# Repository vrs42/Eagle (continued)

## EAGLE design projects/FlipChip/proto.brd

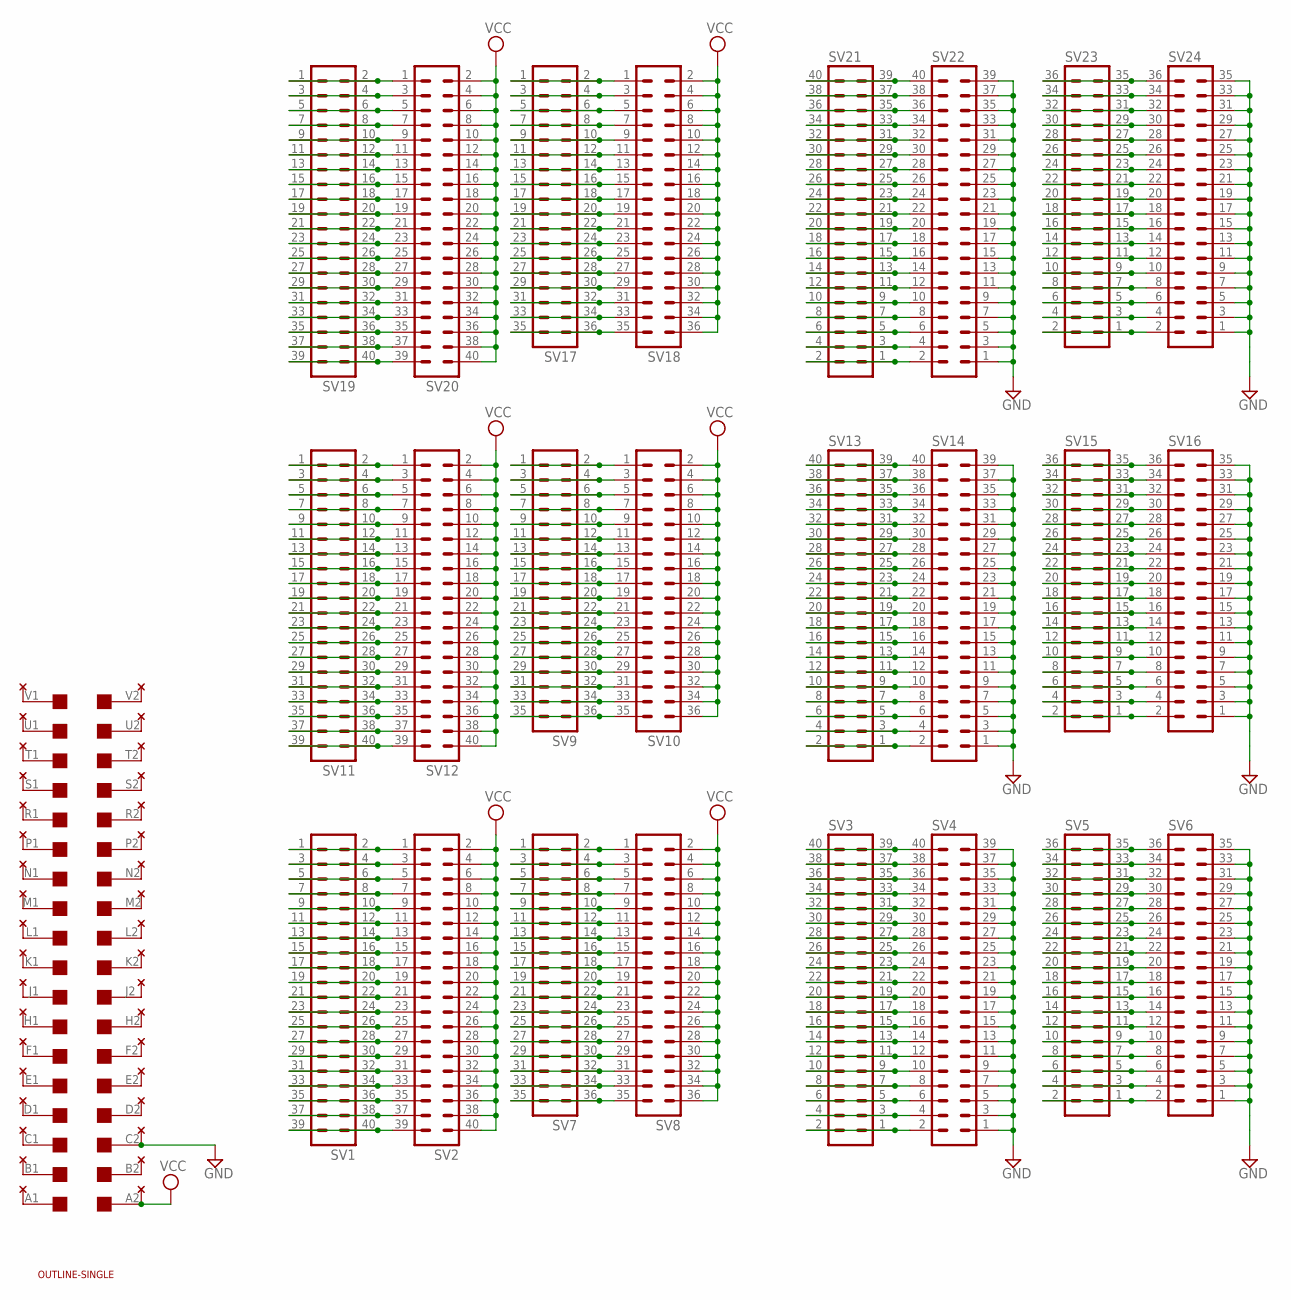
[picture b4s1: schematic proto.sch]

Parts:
SV1, SV2, SV3, SV4, SV11, SV12, SV13, SV14, SV19, SV20, SV21, SV22: MA20-2
SV5, SV6, SV7, SV8, SV9, SV10, SV15, SV16, SV17, SV18, SV23, SV24: MA18-2
U$1: EDGE-2CONNECTOR; EDGE-CON2
U$2: OUTLINE-SINGLE; SINGLE
U$3: THRU-HOLE2A; THRU-HOLEA

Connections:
GND: SV4.1, SV4.3, SV4.5, SV4.7, SV4.9, SV4.11, SV4.13, SV4.15, SV4.17, SV4.19, SV4.21, SV4.23, SV4.25, SV4.27, SV4.29, SV4.31, SV4.33, SV4.35, SV4.37, SV4.39, SV6.1, SV6.3, SV6.5, SV6.7, SV6.9, SV6.11, SV6.13, SV6.15, SV6.17, SV6.19, SV6.21, SV6.23, SV6.25, SV6.27, SV6.29, SV6.31, SV6.33, SV6.35, SV14.1, SV14.3, SV14.5, SV14.7, SV14.9, SV14.11, SV14.13, SV14.15, SV14.17, SV14.19, SV14.21, SV14.23, SV14.25, SV14.27, SV14.29, SV14.31, SV14.33, SV14.35, SV14.37, SV14.39, SV16.1, SV16.3, SV16.5, SV16.7, SV16.9, SV16.11, SV16.13, SV16.15, SV16.17, SV16.19, SV16.21, SV16.23, SV16.25, SV16.27, SV16.29, SV16.31, SV16.33, SV16.35, SV22.1, SV22.3, SV22.5, SV22.7, SV22.9, SV22.11, SV22.13, SV22.15, SV22.17, SV22.19, SV22.21, SV22.23, SV22.25, SV22.27, SV22.29, SV22.31, SV22.33, SV22.35, SV22.37, SV22.39, SV24.1, SV24.3, SV24.5, SV24.7, SV24.9, SV24.11, SV24.13, SV24.15, SV24.17, SV24.19, SV24.21, SV24.23, SV24.25, SV24.27, SV24.29, SV24.31, SV24.33, SV24.35, U$1.C2, U$3.C2
unnamed: U$1.K2, U$3.K2
unnamed: U$1.J2, U$3.J2
unnamed: U$1.H2, U$3.H2
unnamed: U$1.L2, U$3.L2
unnamed: U$1.M2, U$3.M2
unnamed: U$1.N2, U$3.N2
unnamed: U$1.P2, U$3.P2
unnamed: U$1.F2, U$3.F2
unnamed: U$1.E2, U$3.E2
unnamed: U$1.D2, U$3.D2
unnamed: SV1.1, SV1.2, SV2.1
unnamed: U$1.R2, U$3.R2
unnamed: U$1.S2, U$3.S2
unnamed: U$1.B2, U$3.B2
unnamed: SV1.3, SV1.4, SV2.3
unnamed: U$1.T2, U$3.T2
unnamed: U$1.U2, U$3.U2
unnamed: U$1.V2, U$3.V2
unnamed: U$1.A1, U$3.A1
unnamed: U$1.V1, U$3.V1
unnamed: U$1.U1, U$3.U1
unnamed: U$1.T1, U$3.T1
unnamed: U$1.S1, U$3.S1
unnamed: U$1.R1, U$3.R1
unnamed: U$1.P1, U$3.P1
unnamed: U$1.N1, U$3.N1
unnamed: U$1.M1, U$3.M1
unnamed: U$1.L1, U$3.L1
unnamed: U$1.K1, U$3.K1
unnamed: U$1.J1, U$3.J1
unnamed: U$1.H1, U$3.H1
unnamed: U$1.F1, U$3.F1
unnamed: U$1.E1, U$3.E1
unnamed: U$1.D1, U$3.D1
unnamed: U$1.C1, U$3.C1
unnamed: U$1.B1, U$3.B1
unnamed: SV1.5, SV1.6, SV2.5
unnamed: SV7.1, SV7.2, SV8.1
unnamed: SV7.3, SV7.4, SV8.3
unnamed: SV7.5, SV7.6, SV8.5
unnamed: SV7.7, SV7.8, SV8.7
unnamed: SV7.9, SV7.10, SV8.9
unnamed: SV7.11, SV7.12, SV8.11
unnamed: SV7.13, SV7.14, SV8.13
unnamed: SV1.7, SV1.8, SV2.7
unnamed: SV1.9, SV1.10, SV2.9
unnamed: SV1.11, SV1.12, SV2.11
unnamed: SV1.13, SV1.14, SV2.13
unnamed: SV1.15, SV1.16, SV2.15
unnamed: SV1.17, SV1.18, SV2.17
unnamed: SV1.19, SV1.20, SV2.19
unnamed: SV1.21, SV1.22, SV2.21
unnamed: SV1.23, SV1.24, SV2.23
unnamed: SV1.25, SV1.26, SV2.25
unnamed: SV1.27, SV1.28, SV2.27
unnamed: SV1.29, SV1.30, SV2.29
unnamed: SV1.31, SV1.32, SV2.31
unnamed: SV1.33, SV1.34, SV2.33
unnamed: SV1.35, SV1.36, SV2.35
unnamed: SV1.37, SV1.38, SV2.37
unnamed: SV1.39, SV1.40, SV2.39
unnamed: SV7.15, SV7.16, SV8.15
unnamed: SV7.17, SV7.18, SV8.17
unnamed: SV7.19, SV7.20, SV8.19
unnamed: SV7.21, SV7.22, SV8.21
unnamed: SV7.23, SV7.24, SV8.23
unnamed: SV7.25, SV7.26, SV8.25
unnamed: SV7.27, SV7.28, SV8.27
unnamed: SV7.29, SV7.30, SV8.29
unnamed: SV7.31, SV7.32, SV8.31
unnamed: SV7.33, SV7.34, SV8.33
unnamed: SV7.35, SV7.36, SV8.35
unnamed: SV3.39, SV3.40, SV4.40
unnamed: SV3.37, SV3.38, SV4.38
unnamed: SV3.35, SV3.36, SV4.36
unnamed: SV3.33, SV3.34, SV4.34
unnamed: SV3.31, SV3.32, SV4.32
unnamed: SV3.29, SV3.30, SV4.30
unnamed: SV3.27, SV3.28, SV4.28
unnamed: SV3.25, SV3.26, SV4.26
unnamed: SV3.23, SV3.24, SV4.24
unnamed: SV3.21, SV3.22, SV4.22
unnamed: SV3.19, SV3.20, SV4.20
unnamed: SV3.17, SV3.18, SV4.18
unnamed: SV3.15, SV3.16, SV4.16
unnamed: SV3.13, SV3.14, SV4.14
unnamed: SV3.11, SV3.12, SV4.12
unnamed: SV3.9, SV3.10, SV4.10
unnamed: SV3.7, SV3.8, SV4.8
unnamed: SV3.5, SV3.6, SV4.6
unnamed: SV3.3, SV3.4, SV4.4
unnamed: SV3.1, SV3.2, SV4.2
unnamed: SV11.1, SV11.2, SV12.1
unnamed: SV5.35, SV5.36, SV6.36
unnamed: SV5.33, SV5.34, SV6.34
unnamed: SV5.31, SV5.32, SV6.32
unnamed: SV5.29, SV5.30, SV6.30
unnamed: SV5.27, SV5.28, SV6.28
unnamed: SV5.25, SV5.26, SV6.26
unnamed: SV5.23, SV5.24, SV6.24
unnamed: SV5.21, SV5.22, SV6.22
unnamed: SV5.19, SV5.20, SV6.20
unnamed: SV5.17, SV5.18, SV6.18
unnamed: SV5.15, SV5.16, SV6.16
unnamed: SV5.13, SV5.14, SV6.14
unnamed: SV5.11, SV5.12, SV6.12
unnamed: SV5.9, SV5.10, SV6.10
unnamed: SV5.7, SV5.8, SV6.8
unnamed: SV5.5, SV5.6, SV6.6
unnamed: SV5.3, SV5.4, SV6.4
unnamed: SV5.1, SV5.2, SV6.2
unnamed: SV11.3, SV11.4, SV12.3
unnamed: SV11.5, SV11.6, SV12.5
unnamed: SV11.7, SV11.8, SV12.7
unnamed: SV11.9, SV11.10, SV12.9
unnamed: SV11.11, SV11.12, SV12.11
unnamed: SV11.13, SV11.14, SV12.13
unnamed: SV11.15, SV11.16, SV12.15
unnamed: SV11.17, SV11.18, SV12.17
unnamed: SV11.19, SV11.20, SV12.19
unnamed: SV11.21, SV11.22, SV12.21
unnamed: SV11.23, SV11.24, SV12.23
unnamed: SV11.25, SV11.26, SV12.25
unnamed: SV11.27, SV11.28, SV12.27
unnamed: SV11.29, SV11.30, SV12.29
unnamed: SV11.31, SV11.32, SV12.31
unnamed: SV11.33, SV11.34, SV12.33
unnamed: SV11.35, SV11.36, SV12.35
unnamed: SV11.37, SV11.38, SV12.37
unnamed: SV11.39, SV11.40, SV12.39
unnamed: SV9.1, SV9.2, SV10.1
unnamed: SV9.3, SV9.4, SV10.3
unnamed: SV9.5, SV9.6, SV10.5
unnamed: SV9.7, SV9.8, SV10.7
unnamed: SV9.9, SV9.10, SV10.9
unnamed: SV9.11, SV9.12, SV10.11
unnamed: SV9.13, SV9.14, SV10.13
unnamed: SV9.15, SV9.16, SV10.15
unnamed: SV9.17, SV9.18, SV10.17
unnamed: SV9.19, SV9.20, SV10.19
unnamed: SV9.21, SV9.22, SV10.21
unnamed: SV9.23, SV9.24, SV10.23
unnamed: SV9.25, SV9.26, SV10.25
unnamed: SV9.27, SV9.28, SV10.27
unnamed: SV9.29, SV9.30, SV10.29
unnamed: SV9.31, SV9.32, SV10.31
unnamed: SV9.33, SV9.34, SV10.33
unnamed: SV9.35, SV9.36, SV10.35
unnamed: SV13.39, SV13.40, SV14.40
unnamed: SV13.37, SV13.38, SV14.38
unnamed: SV13.35, SV13.36, SV14.36
unnamed: SV13.33, SV13.34, SV14.34
unnamed: SV13.31, SV13.32, SV14.32
unnamed: SV13.29, SV13.30, SV14.30
unnamed: SV13.27, SV13.28, SV14.28
unnamed: SV13.25, SV13.26, SV14.26
unnamed: SV13.23, SV13.24, SV14.24
unnamed: SV13.21, SV13.22, SV14.22
unnamed: SV13.19, SV13.20, SV14.20
unnamed: SV13.17, SV13.18, SV14.18
unnamed: SV13.15, SV13.16, SV14.16
unnamed: SV13.13, SV13.14, SV14.14
unnamed: SV13.11, SV13.12, SV14.12
unnamed: SV13.9, SV13.10, SV14.10
unnamed: SV13.7, SV13.8, SV14.8
unnamed: SV13.5, SV13.6, SV14.6
unnamed: SV13.3, SV13.4, SV14.4
unnamed: SV13.1, SV13.2, SV14.2
unnamed: SV15.35, SV15.36, SV16.36
unnamed: SV15.33, SV15.34, SV16.34
unnamed: SV15.31, SV15.32, SV16.32
unnamed: SV15.29, SV15.30, SV16.30
unnamed: SV15.27, SV15.28, SV16.28
unnamed: SV15.25, SV15.26, SV16.26
unnamed: SV15.23, SV15.24, SV16.24
unnamed: SV15.21, SV15.22, SV16.22
unnamed: SV15.19, SV15.20, SV16.20
unnamed: SV15.17, SV15.18, SV16.18
unnamed: SV15.15, SV15.16, SV16.16
unnamed: SV15.13, SV15.14, SV16.14
unnamed: SV15.11, SV15.12, SV16.12
unnamed: SV15.9, SV15.10, SV16.10
unnamed: SV15.7, SV15.8, SV16.8
unnamed: SV15.5, SV15.6, SV16.6
unnamed: SV15.3, SV15.4, SV16.4
unnamed: SV15.1, SV15.2, SV16.2
unnamed: SV19.1, SV19.2, SV20.1
unnamed: SV19.3, SV19.4, SV20.3
unnamed: SV19.5, SV19.6, SV20.5
unnamed: SV19.7, SV19.8, SV20.7
unnamed: SV19.9, SV19.10, SV20.9
unnamed: SV19.11, SV19.12, SV20.11
unnamed: SV19.13, SV19.14, SV20.13
unnamed: SV19.15, SV19.16, SV20.15
unnamed: SV19.17, SV19.18, SV20.17
unnamed: SV19.19, SV19.20, SV20.19
unnamed: SV19.21, SV19.22, SV20.21
unnamed: SV19.23, SV19.24, SV20.23
unnamed: SV19.25, SV19.26, SV20.25
unnamed: SV19.27, SV19.28, SV20.27
unnamed: SV19.29, SV19.30, SV20.29
unnamed: SV19.31, SV19.32, SV20.31
unnamed: SV19.33, SV19.34, SV20.33
unnamed: SV19.35, SV19.36, SV20.35
unnamed: SV19.37, SV19.38, SV20.37
unnamed: SV19.39, SV19.40, SV20.39
unnamed: SV17.1, SV17.2, SV18.1
unnamed: SV17.3, SV17.4, SV18.3
unnamed: SV17.5, SV17.6, SV18.5
unnamed: SV17.7, SV17.8, SV18.7
unnamed: SV17.9, SV17.10, SV18.9
unnamed: SV17.11, SV17.12, SV18.11
unnamed: SV17.13, SV17.14, SV18.13
unnamed: SV17.15, SV17.16, SV18.15
unnamed: SV17.17, SV17.18, SV18.17
unnamed: SV17.19, SV17.20, SV18.19
unnamed: SV17.21, SV17.22, SV18.21
unnamed: SV17.23, SV17.24, SV18.23
unnamed: SV17.25, SV17.26, SV18.25
unnamed: SV17.27, SV17.28, SV18.27
unnamed: SV17.29, SV17.30, SV18.29
unnamed: SV17.31, SV17.32, SV18.31
unnamed: SV17.33, SV17.34, SV18.33
unnamed: SV17.35, SV17.36, SV18.35
unnamed: SV21.39, SV21.40, SV22.40
unnamed: SV21.37, SV21.38, SV22.38
unnamed: SV21.35, SV21.36, SV22.36
unnamed: SV21.33, SV21.34, SV22.34
unnamed: SV21.31, SV21.32, SV22.32
unnamed: SV21.29, SV21.30, SV22.30
unnamed: SV21.27, SV21.28, SV22.28
unnamed: SV21.25, SV21.26, SV22.26
unnamed: SV21.23, SV21.24, SV22.24
unnamed: SV21.21, SV21.22, SV22.22
unnamed: SV21.19, SV21.20, SV22.20
unnamed: SV21.17, SV21.18, SV22.18
unnamed: SV21.15, SV21.16, SV22.16
unnamed: SV21.13, SV21.14, SV22.14
unnamed: SV21.11, SV21.12, SV22.12
unnamed: SV21.9, SV21.10, SV22.10
unnamed: SV21.7, SV21.8, SV22.8
unnamed: SV21.5, SV21.6, SV22.6
unnamed: SV21.3, SV21.4, SV22.4
unnamed: SV21.1, SV21.2, SV22.2
unnamed: SV23.35, SV23.36, SV24.36
unnamed: SV23.33, SV23.34, SV24.34
unnamed: SV23.31, SV23.32, SV24.32
unnamed: SV23.29, SV23.30, SV24.30
unnamed: SV23.27, SV23.28, SV24.28
unnamed: SV23.25, SV23.26, SV24.26
unnamed: SV23.23, SV23.24, SV24.24
unnamed: SV23.21, SV23.22, SV24.22
unnamed: SV23.19, SV23.20, SV24.20
unnamed: SV23.17, SV23.18, SV24.18
unnamed: SV23.15, SV23.16, SV24.16
unnamed: SV23.13, SV23.14, SV24.14
unnamed: SV23.11, SV23.12, SV24.12
unnamed: SV23.9, SV23.10, SV24.10
unnamed: SV23.7, SV23.8, SV24.8
unnamed: SV23.5, SV23.6, SV24.6
unnamed: SV23.3, SV23.4, SV24.4
unnamed: SV23.1, SV23.2, SV24.2
VCC: SV2.2, SV2.4, SV2.6, SV2.8, SV2.10, SV2.12, SV2.14, SV2.16, SV2.18, SV2.20, SV2.22, SV2.24, SV2.26, SV2.28, SV2.30, SV2.32, SV2.34, SV2.36, SV2.38, SV2.40, SV8.2, SV8.4, SV8.6, SV8.8, SV8.10, SV8.12, SV8.14, SV8.16, SV8.18, SV8.20, SV8.22, SV8.24, SV8.26, SV8.28, SV8.30, SV8.32, SV8.34, SV8.36, SV10.2, SV10.4, SV10.6, SV10.8, SV10.10, SV10.12, SV10.14, SV10.16, SV10.18, SV10.20, SV10.22, SV10.24, SV10.26, SV10.28, SV10.30, SV10.32, SV10.34, SV10.36, SV12.2, SV12.4, SV12.6, SV12.8, SV12.10, SV12.12, SV12.14, SV12.16, SV12.18, SV12.20, SV12.22, SV12.24, SV12.26, SV12.28, SV12.30, SV12.32, SV12.34, SV12.36, SV12.38, SV12.40, SV18.2, SV18.4, SV18.6, SV18.8, SV18.10, SV18.12, SV18.14, SV18.16, SV18.18, SV18.20, SV18.22, SV18.24, SV18.26, SV18.28, SV18.30, SV18.32, SV18.34, SV18.36, SV20.2, SV20.4, SV20.6, SV20.8, SV20.10, SV20.12, SV20.14, SV20.16, SV20.18, SV20.20, SV20.22, SV20.24, SV20.26, SV20.28, SV20.30, SV20.32, SV20.34, SV20.36, SV20.38, SV20.40, U$1.A2, U$3.A2

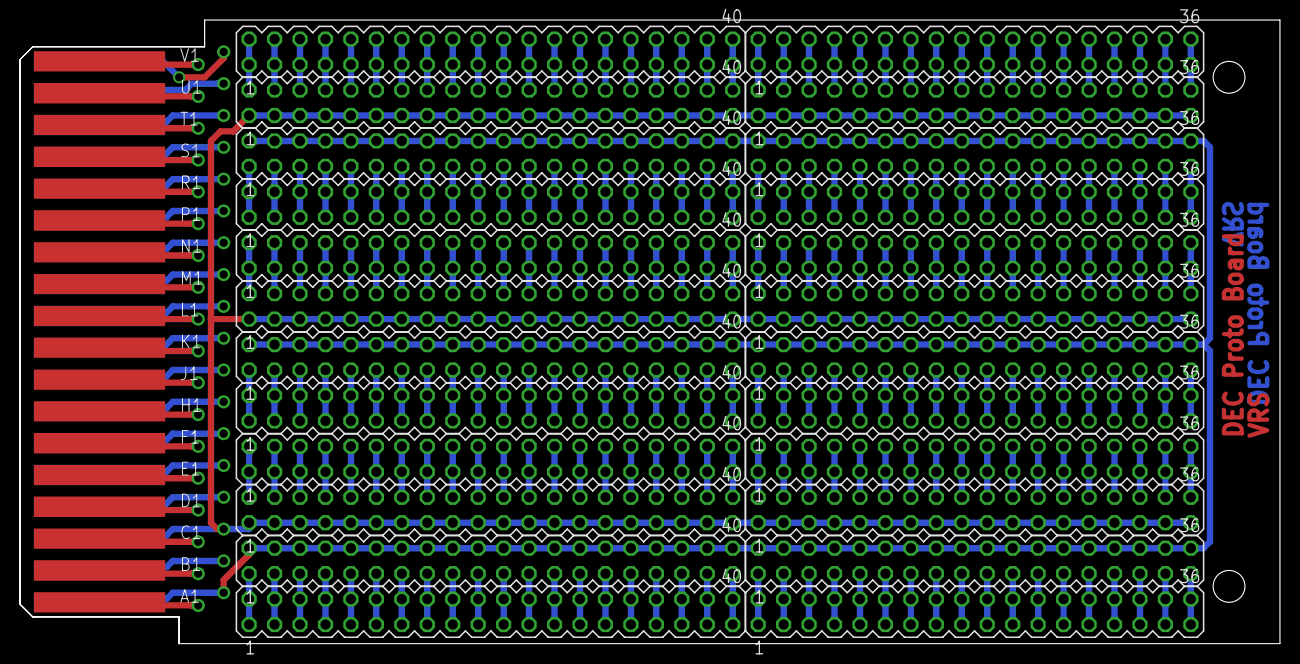
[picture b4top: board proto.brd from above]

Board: 2 copper layers, 125.7 x 62.2 mm, 27 parts (0 on the bottom side), 264 nets.
